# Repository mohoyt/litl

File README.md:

# litl
Litl is an easy to build 40% keyboard using only through hole components. It uses a separate microcontroller (like the Pro Micro or Elite C) to enable flexibility in connectivity and to further simplify the soldering experience (no more tricksy USB ports).

[License](LICENSE)

Litl is licensed under the [Creative Commons Attribution-NonCommercial 4.0 International license](https://creativecommons.org/licenses/by-nc/4.0/). This design as it stands in this repository may be freely reproduced, modified, and manufactured for PERSONAL USE ONLY and may not be reproduced in physical form for public sale. 

Litl kits are available for sale at [sthlmkb.com](https://sthlmkb.com)

## Features
* Only through hole components for easy soldering
* Separate microcontroller using Pro micro, Elite C, Nice! Nano or equivalent footprint. So micro USB, USB-C or Bluetooth are all options!
* 1 or 2 rotary encoders
* OLED screen (though only 1 rotary encoder is possible if using OLED)
* Multiple layout options including split space (2.25u + 1u + 2.75u), split left shift (1.25u + 1u), split enter (1u + 1.25u) and stepped capslock ([layout](http://www.keyboard-layout-editor.com/##@_name=litl&author=mohoyt;&@_x:10.75&c=#82e0f5;&=Enc%202&_x:0.25&w:2.25;&=OLED&_x:0.25&c=#cccccc;&=Enc;&@_y:0.25&x:2.5&w:1.5;&=Esc&=Q&=W&=E&=R&=T&=Y&=U&=I&=O&=P&_w:1.5;&=Back%3Cbr%3ESpace;&@_c=#ebbebe&w:1.25&w2:1.75&l:true;&=Tab&_x:1.25&w:1.75;&=Tab&_c=#cccccc;&=A&=S&=D&=F&=G&=H&=J&=K&=L&_c=#aee6cb&w:2.25;&=Enter;&@_c=#dfe6ba&w:2.25;&=Shift&_x:0.25&w:1.25;&=Shift&=%60%0A~&_c=#cccccc;&=Z&=X&=C&=V&=B&=N&=M&=%3C%0A,&=%3E%0A.&_w:1.75;&=Shift;&@_x:2.5&w:1.25;&=Ctrl&=Alt&_c=#a8abed&w:1.25;&=Cmd&_a:7&w:2.25;&=&_a:4;&=Super&_a:7&w:2.75;&=&_c=#cccccc&a:4&w:1.25;&=Cmd&=Alt&_w:1.25;&=Ctrl;&@_y:0.25&x:4.75&c=#a8abed;&=Cmd&_a:7&w:6.25;&=&_x:1.25&c=#aee6cb&a:4;&='%0A%22&_w:1.25;&=Enter"))
* Open and visible components (in the style of Plaid, Romac etc)
* Simple and flexible case options 

## Components required 
* PCB
* FR4 Switch plate
* FR4 Base 
* Controller (e.g. Pro micro, Elite C, Nice! Nano or something with similar footprint/pinout)
* Switches (5 pin MX footprint) (up to 45)
* Diodes (47)
* Rotary encoders (1 or 2)
* Rotary encoder knobs (1 or 2)
* 0.91" OLED screen 
* 10mm M2 Standoffs (6 required if mounting the base to the plate)
* Acrylic cover for the components at the top (optional)
* Stabilisers (PCB mount) (4 x 2u or 2 x 2u + 6.25u or 2 x 2u depending on layout)
* Rubber feet for the base

[Build guide](build_guide.md)

## Known issues 
Have been fixed in v2 (and gerbers now updated) but were present in v1
- [x] Esc key is missing holes for 5 pin switches (workaround is to cut the pins off that switch to make it 3 pin and with the plate it will still be stable)
- [x] Track routing goes under the front logo and makes it less clear, needs rerouting slightly
- [x] OLED pins are reversed so the OLED has to be mounted facing left (over the diodes) instead of right

Have been fixed in v3 (and gerbers now updated) but were present in later iterations of v2
- [x] Pin for switch alternative on left rotary encoder shorted with ground
- [x] Holes for optional acrylic cover have been readded

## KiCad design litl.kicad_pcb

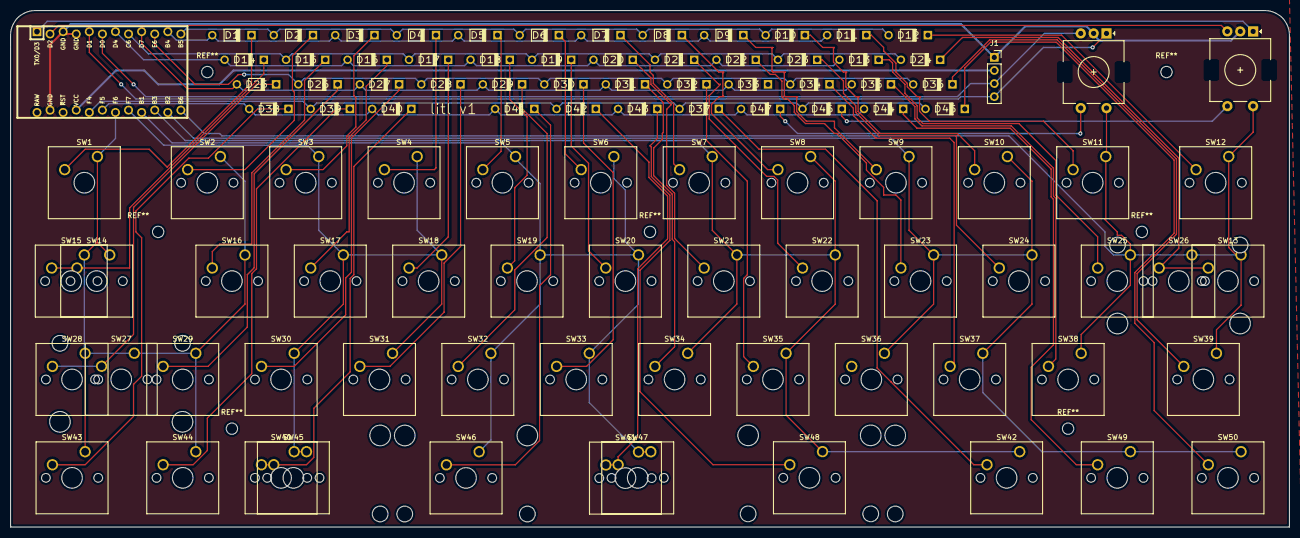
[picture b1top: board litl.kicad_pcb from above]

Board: 2 copper layers, 248.3 x 100.3 mm, 101 parts (1 on the bottom side), 67 nets.

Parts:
D1, D2, D3, D4, D5, D6, D7, D8, D9, D10, D11, D12, D13, D14, D15, D16, D17, D18, D19, D20, D21, D22, D23, D24, D25, D26, D27, D28, D29, D30, D31, D32, D33, D34, D35, D36, D37, D38, D39, D40, D41, D42, D43, D44, D45, D46, D47: D_Small; Diode
J1: Conn_01x04; PinSocket_1x04_P2.54mm_Vertical
SW1: KEYSW; SW_Cherry_MX_1.50u_Plate
SW2, SW3, SW4, SW5, SW6, SW7, SW8, SW9, SW10, SW11, SW15, SW16, SW17, SW18, SW19, SW20, SW21, SW22, SW23, SW24, SW25, SW29, SW30, SW31, SW32, SW33, SW34, SW35, SW36, SW37, SW38, SW40, SW41, SW44, SW49: KEYSW; SW_Cherry_MX_1.00u_PCB
SW12: KEYSW; SW_Cherry_MX_1.50u_PCB
SW13, SW28, SW42, SW43, SW45, SW50: KEYSW; SW_Cherry_MX_1.25u_PCB
SW14, SW39: KEYSW; SW_Cherry_MX_1.75u_PCB
SW26, SW27, SW46: KEYSW; SW_Cherry_MX_2.25u_PCB
SW47: KEYSW; SW_Cherry_MX_6.25u_PCB
SW48: KEYSW; SW_Cherry_MX_2.75u_PCB
SW51, SW53: RotaryEncoder_Switch; RotaryEncoder_EC11
U1: ProMicro; ArduinoProMicro-ZigZag

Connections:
GND: J1.1, SW51.C, SW53.C, U1.3 (GND), U1.4 (GND), U1.23 (GND)
unnamed: D1.2 (A), SW1.2
unnamed: D2.2 (A), SW2.2
unnamed: D3.2 (A), SW3.2
unnamed: D4.2 (A), SW4.2
unnamed: D5.2 (A), SW5.2
unnamed: D6.2 (A), SW6.2
unnamed: D7.2 (A), SW7.2
unnamed: D8.2 (A), SW8.2
unnamed: D9.2 (A), SW9.2
unnamed: D10.2 (A), SW10.2
unnamed: D11.2 (A), SW11.2
unnamed: D12.2 (A), SW12.2
unnamed: D13.2 (A), SW25.2
unnamed: D14.2 (A), SW14.2, SW15.2
unnamed: D15.2 (A), SW16.2
unnamed: D16.2 (A), SW17.2
unnamed: D17.2 (A), SW18.2
unnamed: D18.2 (A), SW19.2
unnamed: D19.2 (A), SW20.2
unnamed: D20.2 (A), SW21.2
unnamed: D21.2 (A), SW22.2
unnamed: D22.2 (A), SW23.2
unnamed: D23.2 (A), SW24.2
unnamed: D24.2 (A), SW13.2, SW26.2
unnamed: D25.2 (A), SW27.2, SW28.2
unnamed: D26.2 (A), SW29.2
unnamed: D27.2 (A), SW30.2
unnamed: D28.2 (A), SW31.2
unnamed: D29.2 (A), SW32.2
unnamed: D30.2 (A), SW33.2
unnamed: D31.2 (A), SW34.2
unnamed: D32.2 (A), SW35.2
unnamed: D33.2 (A), SW36.2
unnamed: D34.2 (A), SW37.2
unnamed: D35.2 (A), SW38.2
unnamed: D36.2 (A), SW39.2
unnamed: D37.2 (A), SW42.2
unnamed: D38.2 (A), SW43.2
unnamed: D39.2 (A), SW44.2
unnamed: D40.2 (A), SW40.2, SW45.2
unnamed: D41.2 (A), SW46.2
unnamed: D42.2 (A), SW41.2, SW47.2
unnamed: D43.2 (A), SW48.2
unnamed: D44.2 (A), SW49.2
unnamed: D45.2 (A), SW50.2
RotA: D46.2 (A), SW51.S1
RotB: SW11.1, SW12.1, SW13.1, SW25.1, SW26.1, SW38.1, SW39.1, SW51.S2, SW53.S2, U1.13 (10/PB6)
RotC: D47.2 (A), SW53.S1
SCL: J1.3, SW53.B, U1.6 (3/PD0)
SDA: J1.4, SW53.A, U1.5 (2/PD1)
VCC: J1.2, U1.21 (VCC)
col0: SW1.1, SW2.1, SW14.1, SW15.1, SW16.1, SW27.1, SW28.1, SW29.1, SW43.1, SW44.1, U1.18 (A1/PF6)
col1: SW3.1, SW4.1, SW17.1, SW18.1, SW30.1, SW31.1, SW40.1, SW45.1, U1.17 (A0/PF7)
col2: SW5.1, SW6.1, SW19.1, SW20.1, SW32.1, SW33.1, SW41.1, SW46.1, SW47.1, U1.16 (15/PB1)
col3: SW7.1, SW8.1, SW21.1, SW22.1, SW34.1, SW35.1, SW42.1, SW48.1, U1.15 (14/PB3)
col4: SW9.1, SW10.1, SW23.1, SW24.1, SW36.1, SW37.1, SW49.1, SW50.1, U1.14 (16/PB2)
encA: SW51.A, U1.1 (TX0/PD3)
encB: SW51.B, U1.2 (RX1/PD2)
rowA: D1.1 (K), D3.1 (K), D5.1 (K), D7.1 (K), D9.1 (K), D11.1 (K), U1.11 (8/PB4)
rowB: D2.1 (K), D4.1 (K), D6.1 (K), D8.1 (K), D10.1 (K), D12.1 (K), U1.12 (9/PB5)
rowC: D13.1 (K), D14.1 (K), D16.1 (K), D18.1 (K), D20.1 (K), D22.1 (K), U1.7 (4/PD4)
rowD: D15.1 (K), D17.1 (K), D19.1 (K), D21.1 (K), D23.1 (K), D24.1 (K), U1.8 (5/PC6)
rowE: D25.1 (K), D27.1 (K), D29.1 (K), D31.1 (K), D33.1 (K), D35.1 (K), U1.9 (6/PD7)
rowF: D26.1 (K), D28.1 (K), D30.1 (K), D32.1 (K), D34.1 (K), D36.1 (K), U1.10 (7/PE6)
rowG: D38.1 (K), D40.1 (K), D41.1 (K), D43.1 (K), D44.1 (K), D47.1 (K), U1.19 (A2/PF5)
rowH: D37.1 (K), D39.1 (K), D42.1 (K), D45.1 (K), D46.1 (K), U1.20 (A3/PF4)

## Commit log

2022-03-13 Kicad setup and added submodules
2022-03-13 Start of matrix
2022-03-13 Schematic complete
2022-03-22 Footprints placed
2022-03-23 Diode layout complete
2022-03-23 Vias added
2022-04-08 Tracks done
2022-04-08 Mounting holes and ground fill done
2022-04-09 Plate and Base added
2022-04-10 Base and plates reworked
2022-04-11 Minimised base size and shrunk top of PCB to make it under 100mm. Send to fab
2022-04-11 Readme updated
2022-04-11 img fixed
2022-04-26 1.5u footprint fixed
2022-04-29 Readme and license updated
2022-05-02 Build guide added
2022-05-04 Build guide link added
2022-05-16 Build guide updated
2022-05-16 buildguide changes
2022-06-07 Gitignore added
2022-06-07 Firmware added
2022-06-08 Remove ds_store
2022-06-08 Readme update
2022-06-27 v2 boards done and test OLED firmware added
2022-06-29 Updated OLED direction
2022-06-29 Updated readme and OLED support
2022-06-29 Updated img
2022-07-18 V2 gerbers for production
2022-08-25 Updated Readme to highlight fixed issues in V2
2022-08-25 Updated pictures for readme
2022-09-16 Bongocat firmware added
2022-11-14 Firmware files refreshed
2022-12-13 Updated silkscreening on board and switch socket option added for encoders. Gerbers v2.1 added
2022-12-16 BlueMicro firmware addition
2022-12-16 Upload uf2 file
2022-12-19 Adjusted readme
2023-01-10 Updated rotary encoder direction in vial firemware files
2023-01-26 Plate file rebuilt and made cleaner. New plate gerbers
2023-04-30 Litl v3 created
2023-04-30 V3 tweaks and new images
2023-08-10 Flashing guide added
2023-11-03 License update
2024-03-25 RP2040 compatible precompiled firmware added
2025-03-20 New base progress
2025-03-21 New base 2025 gerbers added
